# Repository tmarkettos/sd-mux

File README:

sd-mux stands for Secure Digital Multiplexer.

This is SD card switcher (multiplexer) designed to help automatic testing.

This project is sd-mux controller - binary for controlling sd-mux device.

Requirements:
  1. libftdi1 1.2 - development library
  2. popt - development library
  3. cmake - binary tool

Build:
 - enter into project directory
 - create 'build' directory
 - enter into "build" directory
 - run 'cmake ..'
 - run 'make'

Install:
 - enter into 'build' directory
 - run 'sudo make install' to install binary into '/usr/local/bin' (the default one) directory

Note:
If you want to install files into different directory then add argument to cmake command:
 cmake -DCMAKE_INSTALL_PREFIX=/usr ..
Then again run:
 make
 make install

# Upstream

This is a fork of the git repo from https://git.tizen.org/cgit/tools/testlab/sd-mux/
which is described here: https://wiki.tizen.org/SD_MUX

# Modifications

This version has hardware modified by A. Theodore Markettos to:

* Replace the Micro SD socket with a full-size SD card socket, since we need to use a specific SD card with our FPGA. The downstream adapter boards are still Micro SD format, since we can use adaptors to turn Micro SD into SD when needed.
* Refactor some of the components displaced by the SD card socket.
* Rework the relay section so it provides better isolation for mains power, in particular segregating potentially high and low voltage signals. The pin headers have been removed, and wiring rearranged so that 'live' and 'neutral' are not on adjacent pins on the connectors.
* Add fiducials for automated pick and place
* Replace the 8 way headers to the MicroSD adapters with 10 ways, using more common ribbon cables.  Rotate so right-angle connectors can be used.
* Add spare GPIOs on a header, to match relay boards (eg ebay '4 Channel 5V Relay Module Arduino' with header with GND, 4x GPIOs, 5V)
* Current target is DirtyPCBs.com 2-layer process: 0.8mm ENIG for the usd-adaptor, 1.6mm for the main board.

The software interface is unchanged.

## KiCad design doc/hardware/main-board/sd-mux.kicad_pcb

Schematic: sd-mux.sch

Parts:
C1, C2, C4, C5: 27p; C_0805_HandSoldering
C3, C6, C7, C8: 100n; C_0805_HandSoldering
C9: 4.7u; C_0805_HandSoldering
D1, D2: ES1AL; do219ab
FB1: MI0805K400R-10; R_0805_HandSoldering
FID1, FID2, FID3, FID4: Fiducial; Fiducial_1mm_Dia_2.54mm_Outer_CopperTop
J1: 693063020911; mfrn# 693063020911
P1: USB_OTG; conn_usb_B_micro
P2: 629105136821; conn_usb_B_micro
P3, P4: 61400416021; conn_usb_A
P5, P6: Conn_02x05_Odd_Even; IDC-Header_2x05_P2.54mm_Vertical
P7, P10: MKDS 1,5/3; cons_1,5x3
P8: CONN_01X07; PinHeader_1x07_P2.54mm_Vertical
Q1, Q2, Q3, Q4, Q7, Q8: IRF7606PBF; msoic-8
Q5, Q6: 2N7002; SOT-23
R1, R2, R3, R4: 4.7K; R_0805_HandSoldering
R5, R6, R7, R8, R9, R10, R11: 10K; R_0805_HandSoldering
RL1: G2RK-2
U1: TS3USB30EDGSR; msoic-10
U2: FT245RL; ssop-28
U3, U5: 74AHC1G14; SOT-23-5
U4: TS3A27518E; tssop-24

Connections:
/CLK: J1.5 (CLK), U4.7 (COM3)
/CLK_DUT: P5.5, U4.23 (NC3)
/CLK_TS: P6.5, U4.15 (NO3)
/CMD: J1.2 (CMD/MOSI), U4.9 (COM4)
/CMD_DUT: P5.3, U4.21 (NC4)
/CMD_TS: P6.3, U4.17 (NO4)
/DAT0: J1.7 (DAT0/MISO), U4.6 (COM2)
/DAT0_DUT: P5.7, U4.1 (NC2)
/DAT0_TS: P6.7, U4.13 (NO2)
/DAT1: J1.8 (DAT1), U4.4 (COM1)
/DAT1_DUT: P5.8, U4.2 (NC1)
/DAT1_TS: P6.8, U4.11 (NO1)
/DAT2: J1.9 (DAT2), U4.12 (COM6)
/DAT2_DUT: P5.1, U4.22 (NC6)
/DAT2_TS: P6.1, U4.16 (NO6)
/DAT3: J1.1 (CD/DAT3/CS), U4.10 (COM5)
/DAT3_DUT: P5.2, U4.19 (NC5)
/DAT3_TS: P6.2, U4.18 (NO5)
/E: P7.1, P10.1
/GP0: P8.2, U2.5 (D1)
/GP1: P8.3, U2.9 (D5)
/GP2: P8.4, U2.10 (D6)
/GP3: P8.5, U2.6 (D7)
/Lin: P10.2, RL1.6
/Lout: P10.3, RL1.7
/Nin: P7.2, RL1.5
/Nout: P7.3, RL1.4
/POWER_SW_OFF: Q1.4 (G), R6.2, U2.3 (D2)
/POWER_SW_ON: Q2.4 (G), R7.2, U2.2 (D4)
/SOCKET_SEL: Q5.1 (G), R8.2, U2.1 (D0), U3.2, U4.14 (IN2), U4.24 (IN1)
/USB_SEL: Q7.4 (G), R11.2, U1.1 (S), U2.11 (D3), U5.2
/USD_VDD: J1.4 (VDD), Q3.5 (D), Q3.6 (D), Q3.7 (D), Q3.8 (D), Q4.5 (D), Q4.6 (D), Q4.7 (D), Q4.8 (D)
/VDD_DUT: P5.4, Q4.1 (S), Q4.2 (S), Q4.3 (S), R10.1
/VDD_TS: P6.4, Q3.1 (S), Q3.2 (S), Q3.3 (S), R9.1
GND: C1.2, C2.2, C3.2, C4.2, C5.2, C6.2, C7.2, C8.2, C9.2, D1.2 (A), D2.2 (A), J1.3 (GND), J1.6 (GND), J1.GND1, J1.GND2, J1.GND3, J1.GND4, P1.5 (GND), P2.5 (GND), P3.4 (GND), P4.4 (GND), P5.6, P5.9, P5.10, P6.6, P6.9, P6.10, P8.1, Q5.3 (S), Q6.3 (S), R1.2, R2.2, R3.2, R4.2, RL1.9, RL1.10, U1.5 (GND), U1.9 (EN), U2.7 (GND), U2.18 (GND), U2.21 (GND), U2.25 (AGND), U2.26 (TEST), U3.3 (GND), U4.5 (GND), U4.20 (EN), U5.3 (GND)
unnamed: C1.1, P1.6 (shield), R1.1
unnamed: C2.1, P2.6 (shield), R2.1
unnamed: C4.1, P3.5 (shield), R3.1
unnamed: C5.1, P4.5 (shield), R4.1
unnamed: D1.1 (K), Q1.5 (D), Q1.6 (D), Q1.7 (D), Q1.8 (D), RL1.2
unnamed: D2.1 (K), Q2.5 (D), Q2.6 (D), Q2.7 (D), Q2.8 (D), RL1.1
unnamed: FB1.2, P1.1 (VBUS)
unnamed: P1.2 (D-), U2.16 (USBDM)
unnamed: P1.3 (D+), U2.15 (USBDP)
unnamed: P2.1 (VBUS), Q7.1 (S), Q7.2 (S), Q7.3 (S), Q8.1 (S), Q8.2 (S), Q8.3 (S), U5.5 (VCC)
unnamed: P2.2 (D-), U1.6 (D-)
unnamed: P2.3 (D+), U1.4 (D+)
unnamed: P3.1 (VBUS), Q7.5 (D), Q7.6 (D), Q7.7 (D), Q7.8 (D)
unnamed: P3.2 (D-), U1.8 (D1-)
unnamed: P3.3 (D+), U1.2 (D1+)
unnamed: P4.1 (VBUS), Q8.5 (D), Q8.6 (D), Q8.7 (D), Q8.8 (D)
unnamed: P4.2 (D-), U1.7 (D2-)
unnamed: P4.3 (D+), U1.3 (D2+)
unnamed: Q3.4 (G), Q5.2 (D), R9.2
unnamed: Q4.4 (G), Q6.2 (D), R10.2
unnamed: Q6.1 (G), U3.4
unnamed: Q8.4 (G), U5.4
unnamed: R5.2, U2.12 (PWREN#)
VDD: C8.1, C9.1, FB1.1, P8.6, Q1.1 (S), Q1.2 (S), Q1.3 (S), Q2.1 (S), Q2.2 (S), Q2.3 (S), R5.1, R6.1, R7.1, R11.1, U1.10 (VCC), U2.4 (VCCIO), U2.20 (VCC)

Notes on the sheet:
0 - DUT, 1 - TS
SD card socket
Switched MicroUSB host
Switched USB device DUT
Switched USB device TS
SD card output DUT
SD card output TS
MicroUSB host control port
GPIO

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
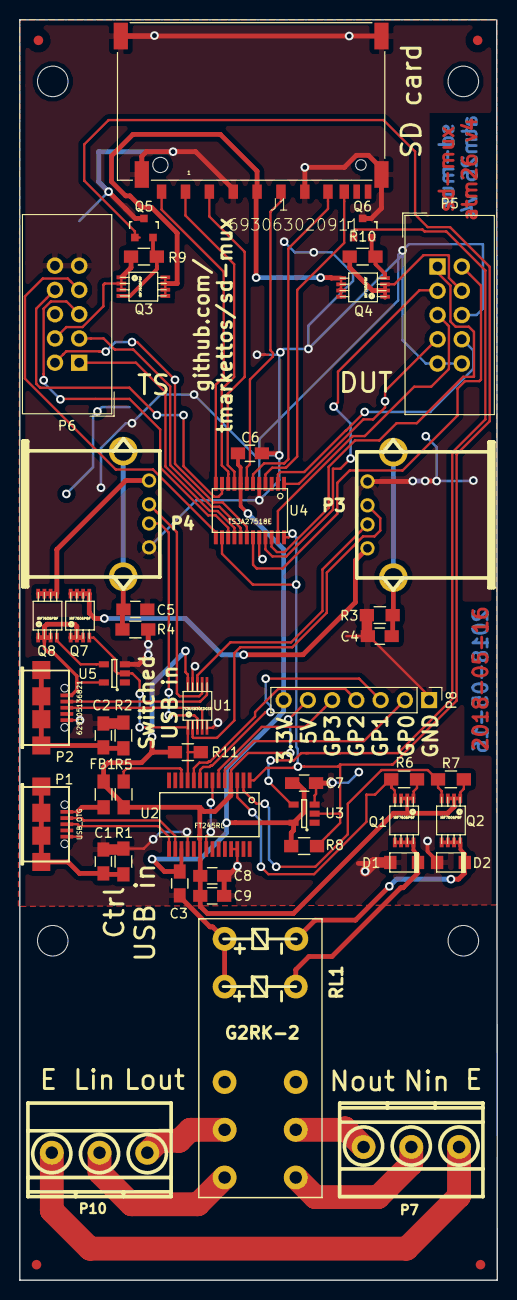
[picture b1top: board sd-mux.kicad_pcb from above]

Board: 2 copper layers, 50.0 x 132.0 mm, 51 parts (0 on the bottom side), 60 nets.

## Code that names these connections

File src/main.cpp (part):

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#define PRODUCT 0x6001
#define SAMSUNG_VENDOR 0x04e8

#define SOCKET_SEL      (0x01 << 0x00)
#define USB_SEL         (0x01 << 0x03)
#define POWER_SW_OFF    (0x01 << 0x02)
#define POWER_SW_ON     (0x01 << 0x04)
#define DYPER1          (0x01 << 0x05)
#define DYPER2          (0x01 << 0x06)

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
int powerOff(struct ftdi_context *ftdi, unsigned char *pins) {
    // Turn on the coil
    *pins |= POWER_SW_ON;
    *pins &= ~(POWER_SW_OFF);
    if (writePins(ftdi, *pins) != EXIT_SUCCESS)
        return EXIT_FAILURE;

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    usleep(DELAY_100MS);

    // Turn off the coil
    *pins |= POWER_SW_OFF;
    if (writePins(ftdi, *pins) != EXIT_SUCCESS)
        return EXIT_FAILURE;

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
int powerOn(struct ftdi_context *ftdi, unsigned char *pins) {
    // Turn on the coil
    *pins |= POWER_SW_OFF;
    *pins &= ~(POWER_SW_ON);
    if (writePins(ftdi, *pins) != EXIT_SUCCESS)
        return EXIT_FAILURE;

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    usleep(DELAY_100MS);

    // Turn off the coil
    *pins |= POWER_SW_ON;
    if (writePins(ftdi, *pins) != EXIT_SUCCESS)
        return EXIT_FAILURE;

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        return EXIT_FAILURE;

    if (target == T_DUT) {
        pins &= ~(USB_SEL);
        pins &= ~(SOCKET_SEL);
        if (powerOn(ftdi, &pins) != EXIT_SUCCESS) {  // Also selects USB and SD
            ret = EXIT_FAILURE;
            goto finish_him;
        }
    } else {
        pins |= USB_SEL;
        pins |= SOCKET_SEL;
        if (powerOff(ftdi, &pins) != EXIT_SUCCESS) { // Also selects USB and SD
            ret = EXIT_FAILURE;
            goto finish_him;
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    ftdi_usb_close(ftdi);
    ftdi_free(ftdi);

    if (!(pins & POWER_SW_ON && pins & POWER_SW_OFF)) {
        fprintf(stdout, "Device not initialized!\n");
        return 0;
    }

    fprintf(stdout, "USB connected to: %s\n", pins & USB_SEL ? "TS" : "DUT");
    fprintf(stdout, "SD connected to: %s\n", pins & SOCKET_SEL ? "TS" : "DUT");

    return 0;
}
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    return ret;
}

int parseArguments(int argc, const char **argv, CCCommand *cmd, int *arg, char *args, size_t argsLen,
                   CCOptionValue options[]) {
    char c;
    char *serial = NULL;
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                *cmd = CCC_TS;
                break;
            case 'p':
                *cmd = CCC_Pins;
                break;
            case 'c':
                *cmd = CCC_Tick;
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
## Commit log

2016-08-12 Add dynamic jumpers (DyPer) control
2017-06-16 Fix power supply connection of USB switch inverter
    Power supply pin of U5 was connected to 3.3V. Q8, driven from this
    inverter, couldn't be fully closed as maximum output voltage from
    the inverter was 3.3V. Now, the inverter, is connected to VCC pin
    of USB connector which gives 5V.
2017-07-18 Add fabrication files for uSD card adapter v 1
2017-07-18 Add fabrication files for main board v 2.1
2017-08-29 Replace Micro SD card with SD card socket. Add fiducials
2017-08-29 Make all vias 0.5mm. Re-lay relay tracks for better isolation
2017-08-29 Refactor relay section so that it obeys mains isolation. Delete headers, rearrange so that 'live' and 'neutral' sections are separated. Rejig pinout so that unused pins never become live, and rotate 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
2017-08-29 Tweak pours to increase clearances. Add some keepouts around ICs where lacking soldermask is likely to be problematic
2017-08-29 Update the README with some explanation
2018-05-17 Fix unrouted tracks
2018-05-17 Move 8w headers up so can fit shrouded 10w versions, flip so can use right angled
2018-05-17 Fix up missing footprints, replace 8w IDC with 10w on PCB so can use common ribbon cables
2018-05-17 Pin out spare GPIOs to a header, eg to match ebay '4 channel relay module Arduino RPi'
2018-05-17 Label up inputs and add URL in silk
2018-05-17 Move up IDC connector to be symmetrical
2018-05-17 Make usd-adapter fabrication outputs DirtyPCBs friendly
2018-05-17 Describe recent changes in the README
2018-05-17 Remove origin mark that confuses DirtyPCBs
2018-05-17 Add fabrication files for v4.0
2018-05-17 Rename fabrication files to match existing
2018-05-17 Respin usd-adapter with silk and soldermask

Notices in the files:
src/main.cpp:
Copyright (c) 2016 Samsung Electronics Co., Ltd All Rights Reserved
Licensed under the Apache License, Version 2.0 (the "License");
See the License for the specific language governing permissions and
limitations under the License
